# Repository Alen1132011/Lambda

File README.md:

# Lambda Terminal

This is a Half-Life themed controller I designed around an ESP32-S3. It has a rotary encoder, three Choc switches, a little OLED and a buzzer, but the part I'm most excited about is the touch stuff: a honeycomb of three hex pads and a four segment zigzag slider, all made out of copper on the PCB itself. No moving parts, no extra chips.

The board is exactly 100 x 100 mm, which keeps it in JLCPCB's cheapest size tier. It also has a big lambda on it, because of course it does.

## Features

- Waveshare ESP32-S3-Zero, so native USB
- 3 hex capacitive touch pads (12 mm flat to flat) in a honeycomb
- 4 segment zigzag touch slider, which gives you a position instead of just on/off
- EC11 rotary encoder
- 3x Kailh Choc low profile switches
- I2C OLED
- Buzzer
- 100 x 100 mm, 2 layers, rounded corners and 4 mounting holes
- Lambda logo in exposed copper and hazard stripes on the silkscreen

## Case

There isn't one yet. For now it's just the board, with 4 M3 holes in the corners so you can put it on standoffs.

## PCB

Here's the schematic and the board. Everything was made in KiCad.

A few things I want to say about it:

- The touch pads are an ESP32-S3 thing. The chip can read capacitance on GPIO 1 to 14 by itself, so I didn't need a separate touch IC. I did think about an MPR121, but I only needed 7 channels and the S3 has enough.
- The pads are covered by solder mask. It's thin enough that touch still works, and your finger never touches bare copper.
- The touch traces go to the back of the board through a via and stay away from the other signals, because anything running near a touch pad ends up affecting it.
- They're long though (somewhere between 35 and 85 mm), so expect to tune the thresholds in firmware.
- I wanted orange pads. JLCPCB doesn't have an orange solder mask, and their silkscreen is white only, so the board is black with white text and the lambda is exposed copper. If you order ENIG it comes out gold, with HASL it's silver.
### Pin map

| Part | GPIO |
|---|---|
| Hex pad 1, 2, 3 | 1, 2, 3 |
| Slider segments (top to bottom) | 8, 9, 6, 7 |
| Encoder A, B | 10, 11 |
| Switch 1, 2, 3 | 12, 44 (RX), 43 (TX) |
| Buzzer | 13 |
| OLED SCL, SDA | 4, 5 |

The switches and the encoder go to GND, so use internal pull-ups.

## Firmware Overview

Nothing is flashed yet, the firmware is the next thing on the list. This is the plan:

- Show up as a USB MIDI device over the S3's native USB
- Hex pads play notes
- The slider sends a continuous value (position 0 to 127)
- The encoder changes volume
- The switches do octave down, octave up and sustain
- The OLED shows what's going on and the buzzer clicks when you hit something

## BOM

- 1x Waveshare ESP32-S3-Zero
- 1x EC11 rotary encoder with push switch
- 3x Kailh Choc low profile switches (and keycaps if you want them)
- 1x 128x64 I2C OLED (SSD1306)
- 1x buzzer, 12 mm
- 1x PCB, 100 x 100 mm
- 4x M3 screws and standoffs (optional)

One heads up on the OLED: the footprint is the 8 pin Adafruit SSD1306 breakout, so check that your module actually matches it before you order the boards. A lot of the cheap 4 pin ones don't.

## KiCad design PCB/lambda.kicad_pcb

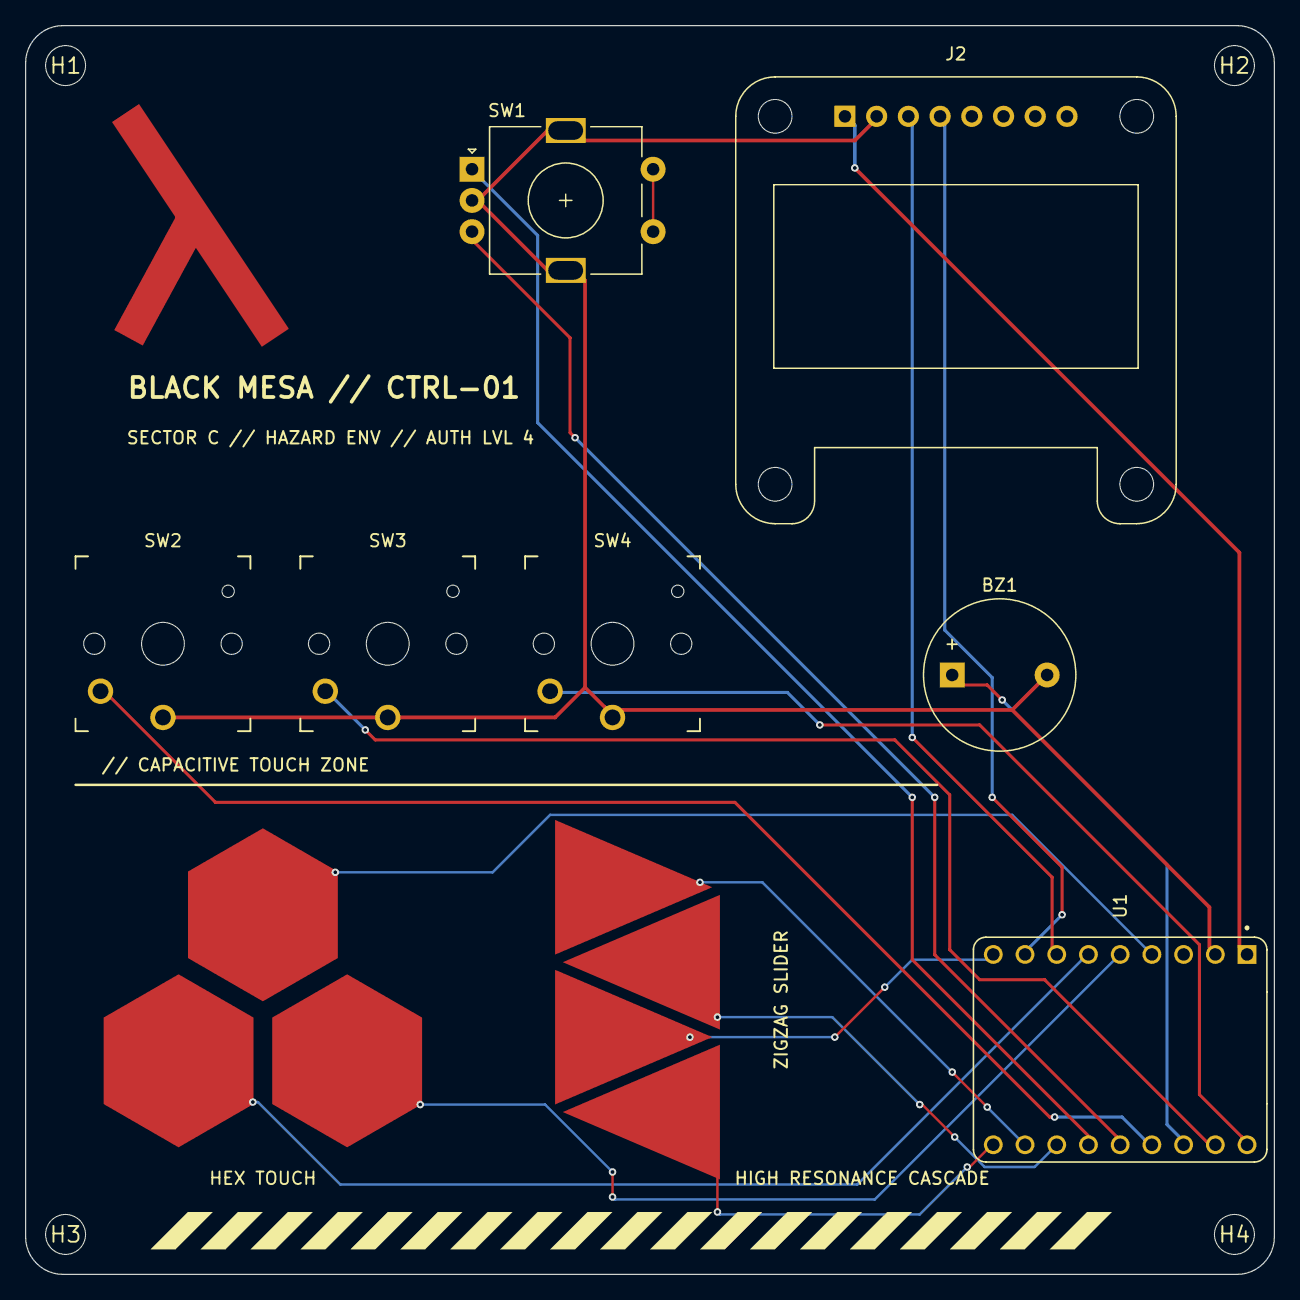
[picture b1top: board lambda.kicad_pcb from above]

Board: 2 copper layers, 100.0 x 100.0 mm, 13 parts (0 on the bottom side), 17 nets.

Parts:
BZ1: Buzzer; Buzzer_12x9.5RM7.6
H1, H2, H3, H4: MountingHole_3.2mm
J2: Conn_01x04_Pin; Adafruit_SSD1306
J3: Conn_01x03_Pin; TouchHoneycomb3_12mm_Covered
J4: Conn_01x04_Pin; TouchZigzag4_Covered
SW1: RotaryEncoder_Switch_MP; RotaryEncoder_Alps_EC11E-Switch_Vertical_H20mm
SW2, SW3, SW4: SW_Push; Kailh Choc Low-Profile Switches
U1: Waveshare ESP32-S3-ZERO; Waveshare ESP32-S3-Zero

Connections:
+3.3V: J2.1, U1.5V
/EC 1: SW1.A, U1.10 (GP10)
/EC 2: SW1.B, U1.11 (GP11)
/SCL: J2.3, U1.4 (GP4)
/SDA: J2.4, U1.5 (GP5)
/TOUCH1: J3.1, U1.1 (GP1)
/TOUCH2: J3.2, U1.2 (GP2)
/TOUCH3: J3.3, U1.3 (GP3)
/TOUCH4: J4.1, U1.8 (GP8)
/TOUCH5: J4.2, U1.9 (GP9)
/TOUCH6: J4.3, U1.6 (GP6)
/TOUCH7: J4.4, U1.7 (GP7)
/ec3: BZ1.1 (+), U1.13 (GP13)
/switch1: SW2.2, U1.12 (GP12)
/switch2: SW3.2, U1.RX
/switch3: SW4.2, U1.TX
GND: BZ1.2 (-), J2.2, SW1.C, SW1.MP, SW2.1, SW3.1, SW4.1, U1.GND
